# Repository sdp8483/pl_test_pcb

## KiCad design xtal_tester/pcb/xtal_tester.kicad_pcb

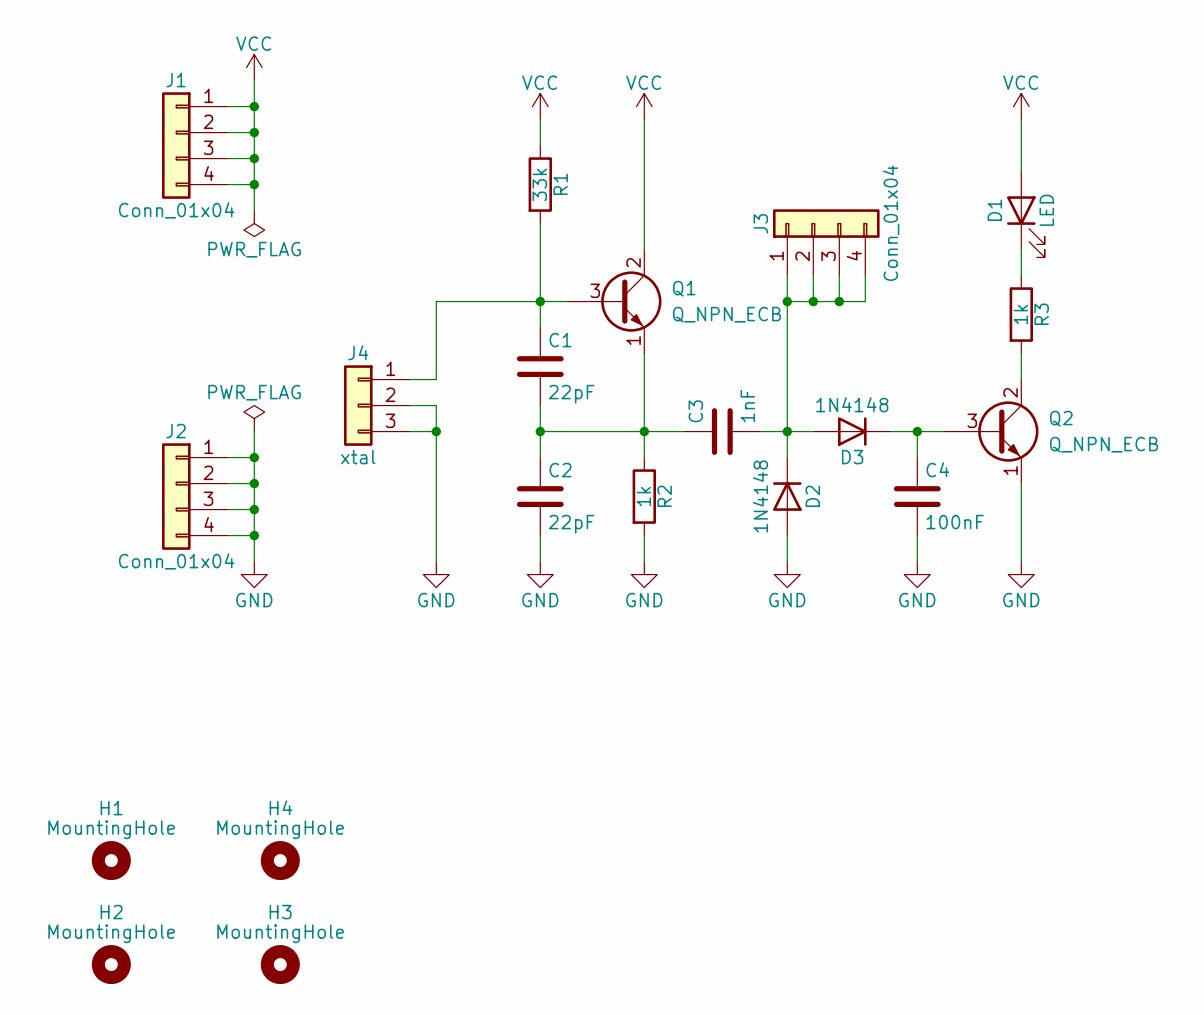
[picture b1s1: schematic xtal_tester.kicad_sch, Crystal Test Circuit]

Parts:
C1, C2: 22pF; C_Disc_D4.3mm_W1.9mm_P5.00mm
C3: 1nF; C_Rect_L7.0mm_W2.5mm_P5.00mm
C4: 100nF; C_Axial_L3.8mm_D2.6mm_P7.50mm_Horizontal
D1: LED; LED_D3.0mm
D2, D3: 1N4148; D_DO-35_SOD27_P7.62mm_Horizontal
H1, H2, H3, H4: MountingHole; MountingHole_3.2mm_M3
J1, J2, J3: Conn_01x04; PinHeader_1x04_P2.54mm_Vertical
J4: xtal; PinHeader_1x03_P2.54mm_Vertical
Q1, Q2: Q_NPN_ECB; TO-92_Inline_Wide
R1: 33k; R_Axial_DIN0207_L6.3mm_D2.5mm_P10.16mm_Horizontal
R2, R3: 1k; R_Axial_DIN0207_L6.3mm_D2.5mm_P10.16mm_Horizontal

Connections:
GND: C2.2, C4.2, D2.2 (A), J2.1, J2.2, J2.3, J2.4, J4.2, J4.3, Q2.1 (E), R2.2
unnamed: D1.1 (K), R3.1
unnamed: C3.2, D2.1 (K), D3.2 (A), J3.1, J3.2, J3.3, J3.4
unnamed: C4.1, D3.1 (K), Q2.3 (B)
unnamed: C1.1, J4.1, Q1.3 (B), R1.2
unnamed: C1.2, C2.1, C3.1, Q1.1 (E), R2.1
unnamed: Q2.2 (C), R3.2
VCC: D1.2 (A), J1.1, J1.2, J1.3, J1.4, Q1.2 (C), R1.1

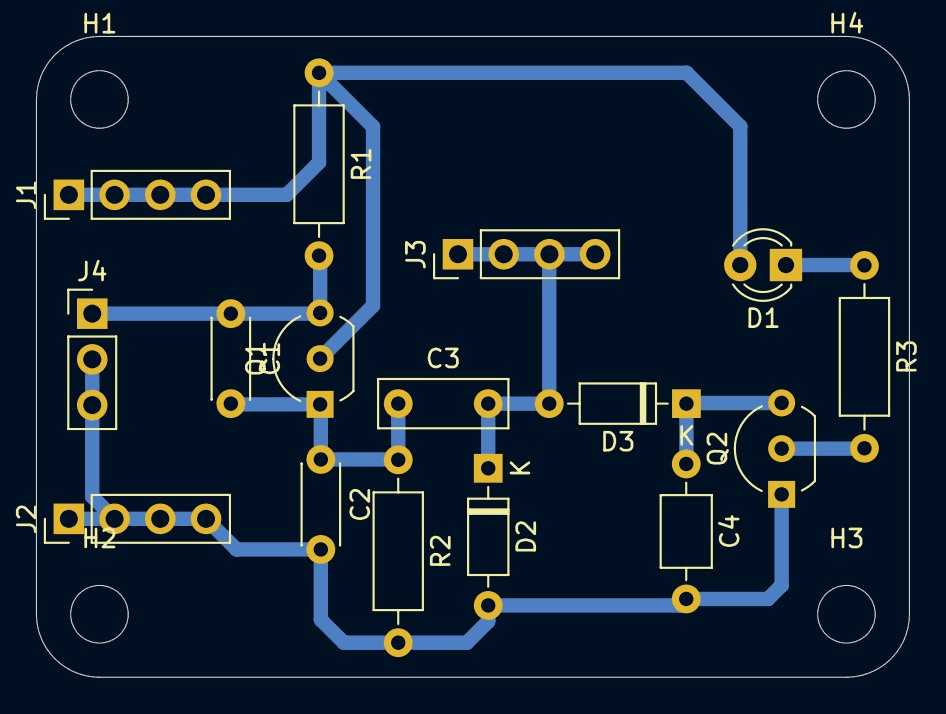
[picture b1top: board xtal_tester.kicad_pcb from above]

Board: 2 copper layers, 48.5 x 35.6 mm, 20 parts (0 on the bottom side), 8 nets.
